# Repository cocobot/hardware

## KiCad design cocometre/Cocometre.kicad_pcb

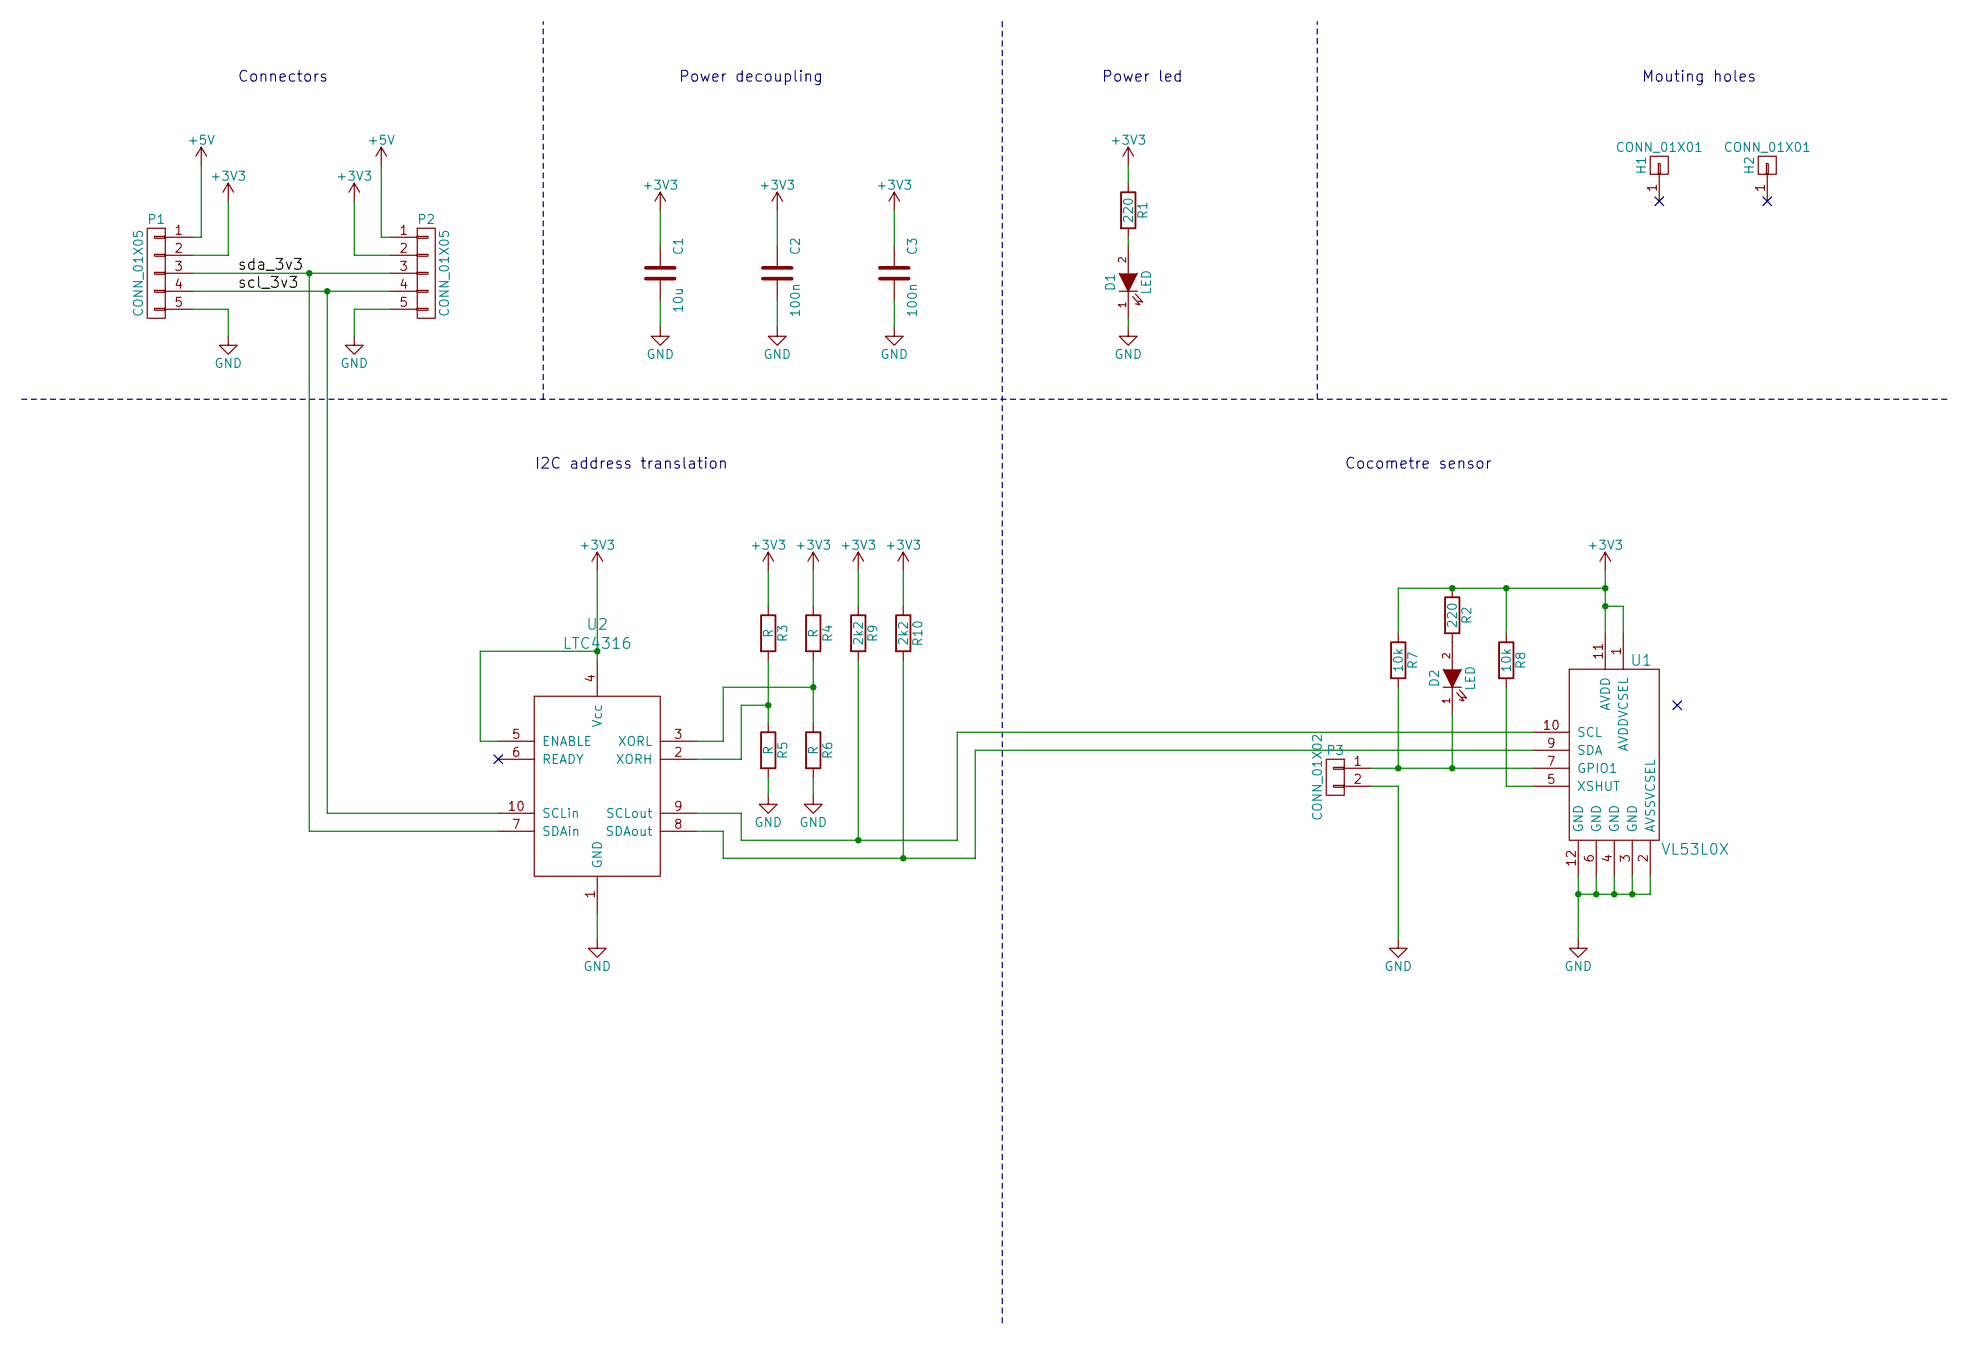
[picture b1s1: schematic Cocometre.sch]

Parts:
C1: 10u; C_0805_HandSoldering
C2, C3: 100n; C_0603_HandSoldering
D1, D2: LED; LED_0805
H1, H2: CONN_01X01; MountingHole_3.2mm_M3
P1, P2: CONN_01X05; Socket_MOLEX-KK-RM2-54mm_Lock_5pin_straight
P3: CONN_01X02; Socket_MOLEX-KK-RM2-54mm_Lock_2pin_straight
R1, R2: 220; R_0603_HandSoldering
R3, R4, R5, R6: R; R_0603_HandSoldering
R7, R8: 10k; R_0603_HandSoldering
R9, R10: 2k2; R_0603_HandSoldering
U1: VL53L0X
U2: LTC4316; MSOP-10

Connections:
+3V3: C1.1, C2.1, C3.1, P1.2, P2.2, R1.1, R2.1, R3.1, R4.1, R7.1, R8.1, R9.1, R10.1, U1.1 (AVDDVCSEL), U1.11 (AVDD), U2.4 (Vcc), U2.5 (ENABLE)
+5V: P1.1, P2.1
/scl_3v3: P1.4, P2.4, U2.10 (SCLin)
/sda_3v3: P1.3, P2.3, U2.7 (SDAin)
GND: C1.2, C2.2, C3.2, D1.1 (K), P1.5, P2.5, P3.2, R5.2, R6.2, U1.2 (AVSSVCSEL), U1.3 (GND), U1.4 (GND), U1.6 (GND), U1.12 (GND), U2.1 (GND)
unnamed: D1.2 (A), R1.2
unnamed: D2.1 (K), P3.1, R7.2, U1.7 (GPIO1)
unnamed: D2.2 (A), R2.2
unnamed: R3.2, R5.1, U2.2 (XORH)
unnamed: R4.2, R6.1, U2.3 (XORL)
unnamed: R8.2, U1.5 (XSHUT)
unnamed: R9.2, U1.10 (SCL), U2.9 (SCLout)
unnamed: R10.2, U1.9 (SDA), U2.8 (SDAout)

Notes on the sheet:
Connectors
Power decoupling
I2C address translation
Cocometre sensor
Mouting holes
Power led

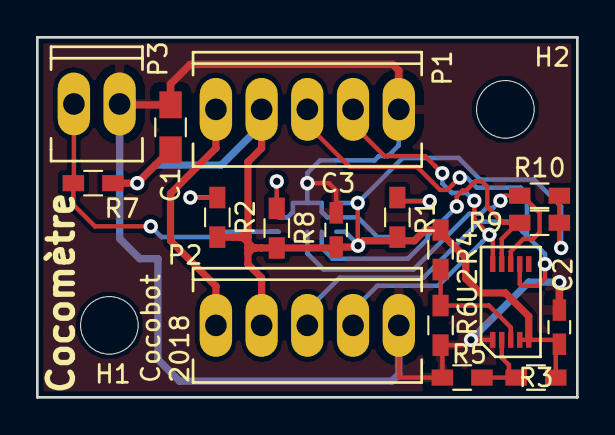
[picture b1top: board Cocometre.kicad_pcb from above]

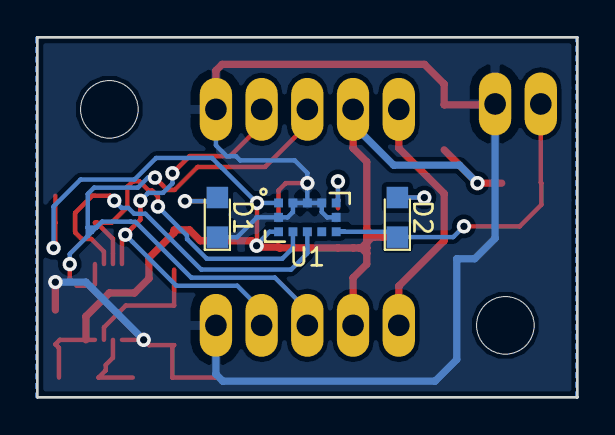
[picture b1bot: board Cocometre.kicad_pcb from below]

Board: 2 copper layers, 30.0 x 20.0 mm, 22 parts (3 on the bottom side), 13 nets.

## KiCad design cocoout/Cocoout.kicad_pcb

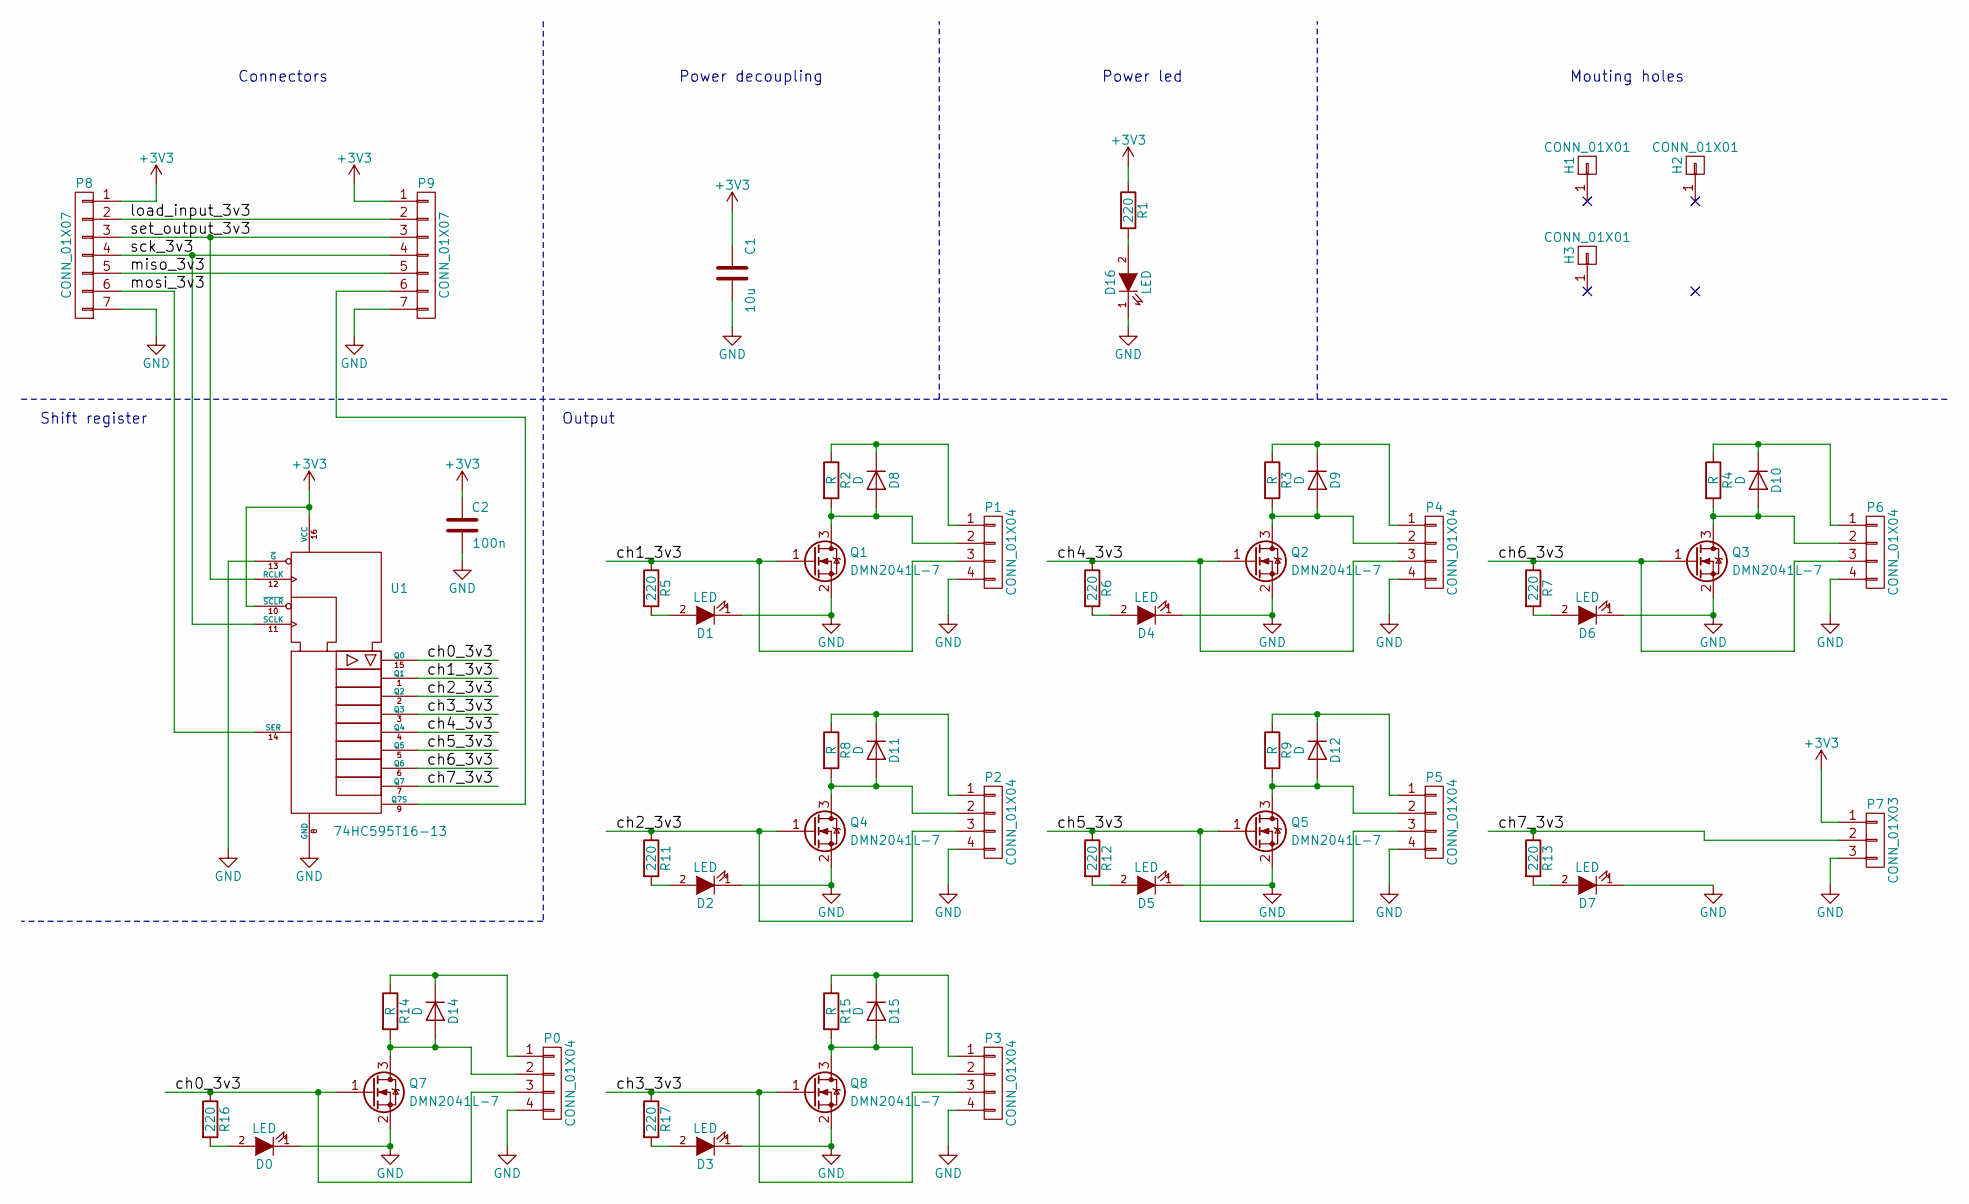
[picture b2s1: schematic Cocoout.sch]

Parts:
C1: 10u; C_0805_HandSoldering
C2: 100n; C_0603_HandSoldering
D0, D1, D2, D3, D4, D5, D6, D7, D16: LED; D_0805
D8, D9, D10, D11, D12, D14, D15: D; D_SMA_Handsoldering
H1, H2, H3: CONN_01X01; MountingHole_3.2mm_M3
P0, P1, P2, P3, P4, P5, P6: CONN_01X04; Socket_MOLEX-KK-RM2-54mm_Lock_4pin_straight
P7: CONN_01X03; Socket_MOLEX-KK-RM2-54mm_Lock_3pin_straight
P8, P9: CONN_01X07; Socket_MOLEX-KK-RM2-54mm_Lock_7pin_straight
Q1, Q2, Q3, Q4, Q5, Q7, Q8: DMN2041L-7; SOT-23
R1, R5, R6, R7, R11, R12, R13, R16, R17: 220; R_0603_HandSoldering
R2, R3, R4, R8, R9, R14, R15: R; R_0603_HandSoldering
U1: 74HC595T16-13; TSSOP-16_4.4x5mm_Pitch0.65mm

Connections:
+3V3: C1.1, C2.1, P7.1, P8.1, P9.1, R1.1, U1.10 (~SCLR), U1.16 (VCC)
/ch0_3v3: P0.3, Q7.1 (G), R16.1, U1.15 (Q0)
/ch1_3v3: P1.3, Q1.1 (G), R5.1, U1.1 (Q1)
/ch2_3v3: P2.3, Q4.1 (G), R11.1, U1.2 (Q2)
/ch3_3v3: P3.3, Q8.1 (G), R17.1, U1.3 (Q3)
/ch4_3v3: P4.3, Q2.1 (G), R6.1, U1.4 (Q4)
/ch5_3v3: P5.3, Q5.1 (G), R12.1, U1.5 (Q5)
/ch6_3v3: P6.3, Q3.1 (G), R7.1, U1.6 (Q6)
/ch7_3v3: P7.2, R13.1, U1.7 (Q7)
/load_input_3v3: P8.2, P9.2
/miso_3v3: P8.5, P9.5
/mosi_3v3: P8.6, U1.14 (SER)
/sck_3v3: P8.4, P9.4, U1.11 (SCLK)
/set_output_3v3: P8.3, P9.3, U1.12 (RCLK)
GND: C1.2, C2.2, D0.1 (K), D1.1 (K), D2.1 (K), D3.1 (K), D4.1 (K), D5.1 (K), D6.1 (K), D7.1 (K), D16.1 (K), P0.4, P1.4, P2.4, P3.4, P4.4, P5.4, P6.4, P7.3, P8.7, P9.7, Q1.2 (S), Q2.2 (S), Q3.2 (S), Q4.2 (S), Q5.2 (S), Q7.2 (S), Q8.2 (S), U1.8 (GND), U1.13 (~G)
unnamed: D0.2 (A), R16.2
unnamed: D1.2 (A), R5.2
unnamed: D2.2 (A), R11.2
unnamed: D3.2 (A), R17.2
unnamed: D4.2 (A), R6.2
unnamed: D5.2 (A), R12.2
unnamed: D6.2 (A), R7.2
unnamed: D7.2 (A), R13.2
unnamed: D8.1 (K), P1.1, R2.1
unnamed: D8.2 (A), P1.2, Q1.3 (D), R2.2
unnamed: D9.1 (K), P4.1, R3.1
unnamed: D9.2 (A), P4.2, Q2.3 (D), R3.2
unnamed: D10.1 (K), P6.1, R4.1
unnamed: D10.2 (A), P6.2, Q3.3 (D), R4.2
unnamed: D11.1 (K), P2.1, R8.1
unnamed: D11.2 (A), P2.2, Q4.3 (D), R8.2
unnamed: D12.1 (K), P5.1, R9.1
unnamed: D12.2 (A), P5.2, Q5.3 (D), R9.2
unnamed: D14.1 (K), P0.1, R14.1
unnamed: D14.2 (A), P0.2, Q7.3 (D), R14.2
unnamed: D15.1 (K), P3.1, R15.1
unnamed: D15.2 (A), P3.2, Q8.3 (D), R15.2
unnamed: D16.2 (A), R1.2
unnamed: P9.6, U1.9 (Q7S)

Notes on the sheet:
Connectors
Power decoupling
Mouting holes
Power led
Output
Shift register

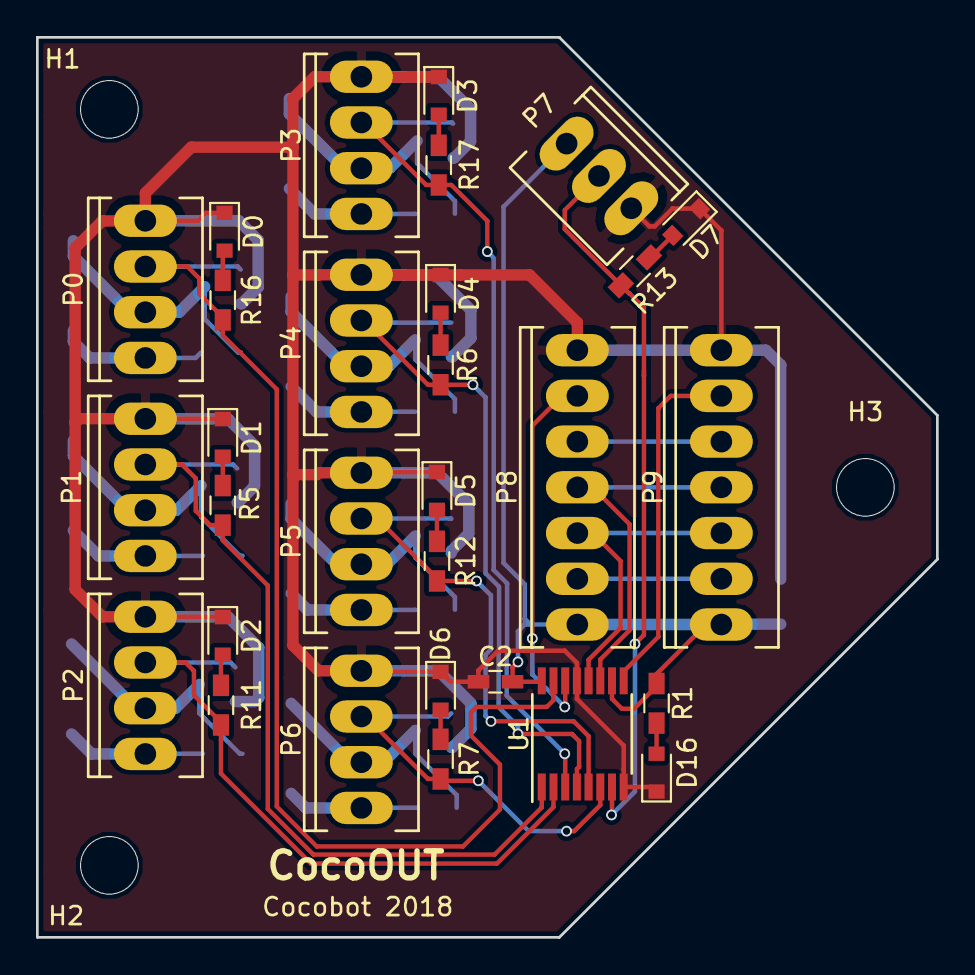
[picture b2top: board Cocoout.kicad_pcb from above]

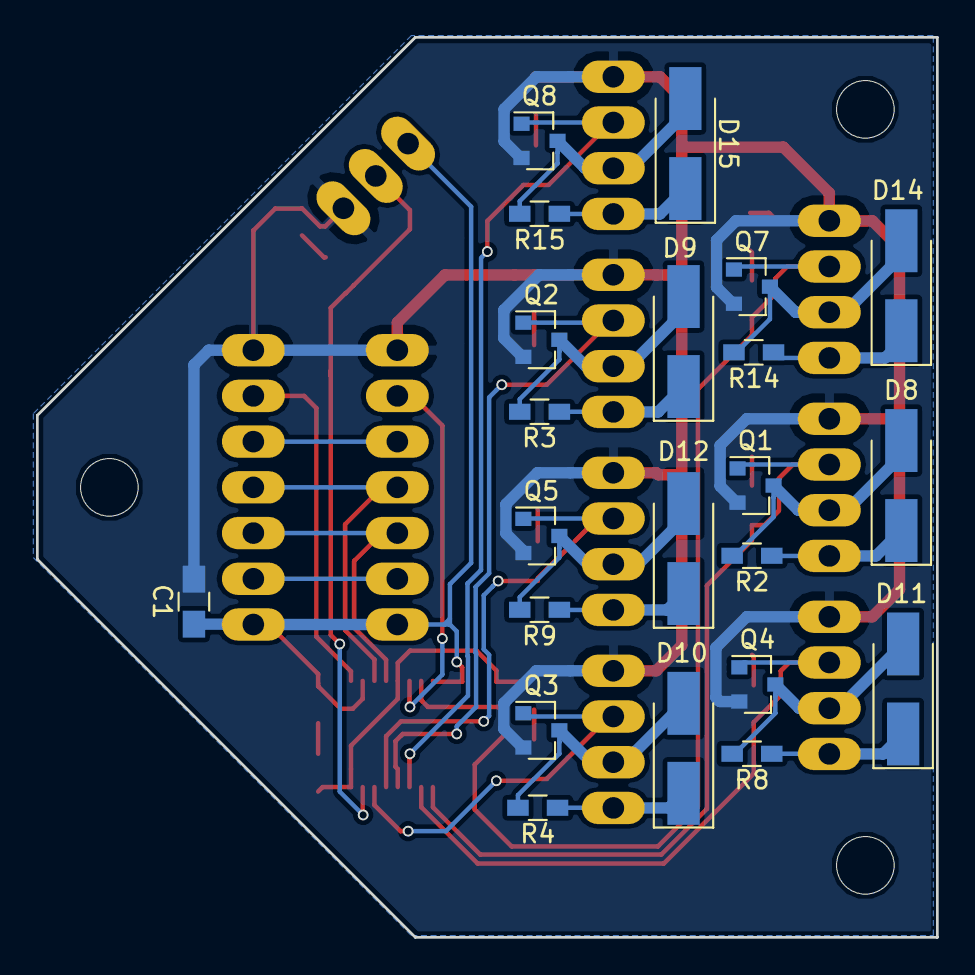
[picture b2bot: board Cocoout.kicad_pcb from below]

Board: 2 copper layers, 50.0 x 50.0 mm, 55 parts (22 on the bottom side), 39 nets.

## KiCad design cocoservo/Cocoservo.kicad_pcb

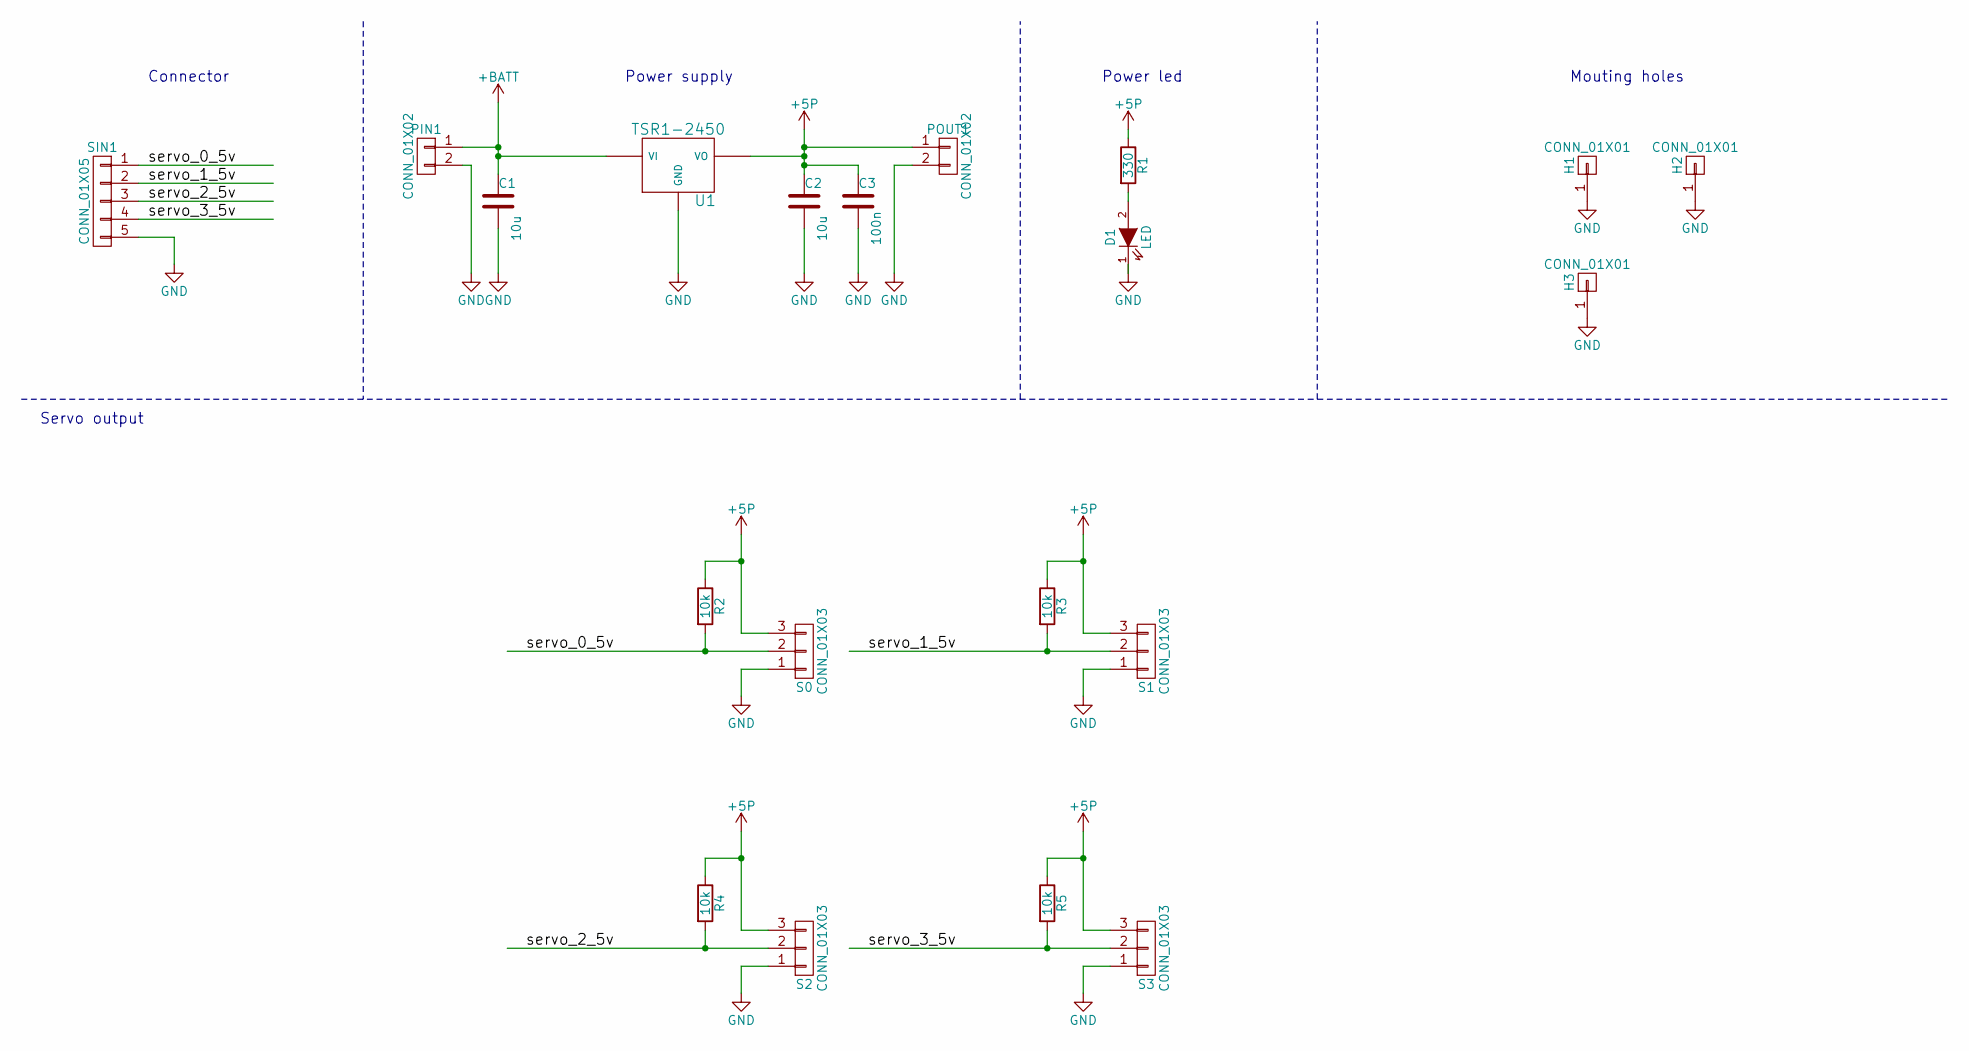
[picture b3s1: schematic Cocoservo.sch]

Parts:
C1, C2: 10u; C_0805_HandSoldering
C3: 100n; C_0603_HandSoldering
D1: LED; LED_0805
H1, H2, H3: CONN_01X01; MountingHole_3.2mm_M3
PIN1: CONN_01X02; Socket_MOLEX-KK-RM2-54mm_Lock_2pin_straight
POUT1: CONN_01X02; Socket_MOLEX-KK-RM2-54mm_Lock_2pin_straight
R1: 330; R_0603_HandSoldering
R2, R3, R4, R5: 10k; R_0603_HandSoldering
S0, S1, S2, S3: CONN_01X03; Socket_MOLEX-KK-RM2-54mm_Lock_3pin_straight
SIN1: CONN_01X05; Socket_MOLEX-KK-RM2-54mm_Lock_5pin_straight
U1: TSR1-2450; TSR-1

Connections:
+5P: C2.1, C3.1, POUT1.1, R1.1, R2.1, R3.1, R4.1, R5.1, S0.3, S1.3, S2.3, S3.3, U1.3 (VO)
+BATT: C1.1, PIN1.1, U1.1 (VI)
/servo_0_5v: R2.2, S0.2, SIN1.1
/servo_1_5v: R3.2, S1.2, SIN1.2
/servo_2_5v: R4.2, S2.2, SIN1.3
/servo_3_5v: R5.2, S3.2, SIN1.4
GND: C1.2, C2.2, C3.2, D1.1 (K), H1.1, H2.1, H3.1, PIN1.2, POUT1.2, S0.1, S1.1, S2.1, S3.1, SIN1.5, U1.2 (GND)
unnamed: D1.2 (A), R1.2

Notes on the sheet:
Connector
Mouting holes
Power led
Servo output
Power supply

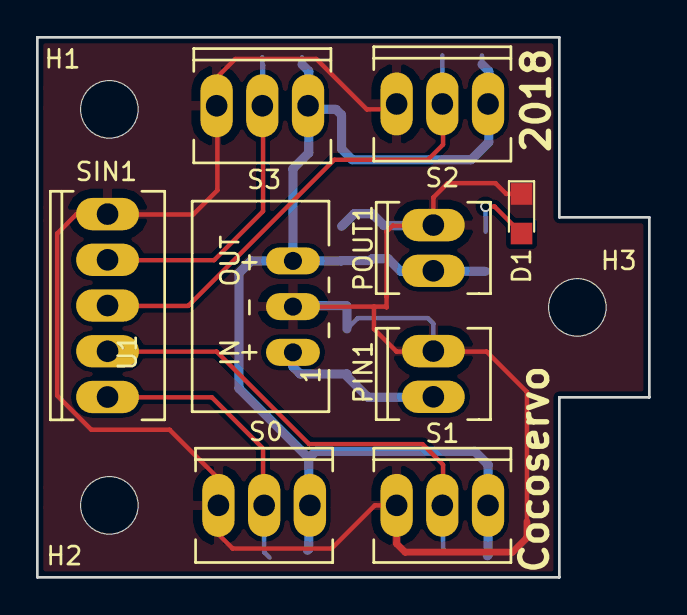
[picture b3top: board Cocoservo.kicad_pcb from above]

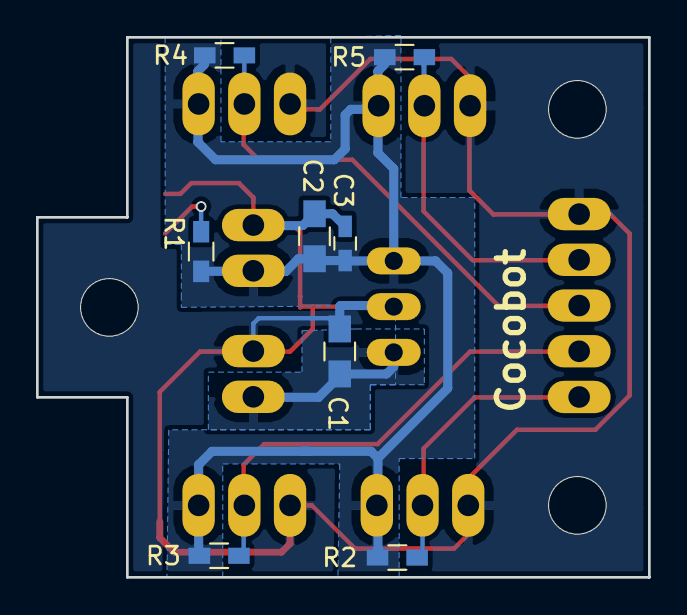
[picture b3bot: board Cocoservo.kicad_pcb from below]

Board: 2 copper layers, 34.0 x 30.0 mm, 20 parts (8 on the bottom side), 8 nets.

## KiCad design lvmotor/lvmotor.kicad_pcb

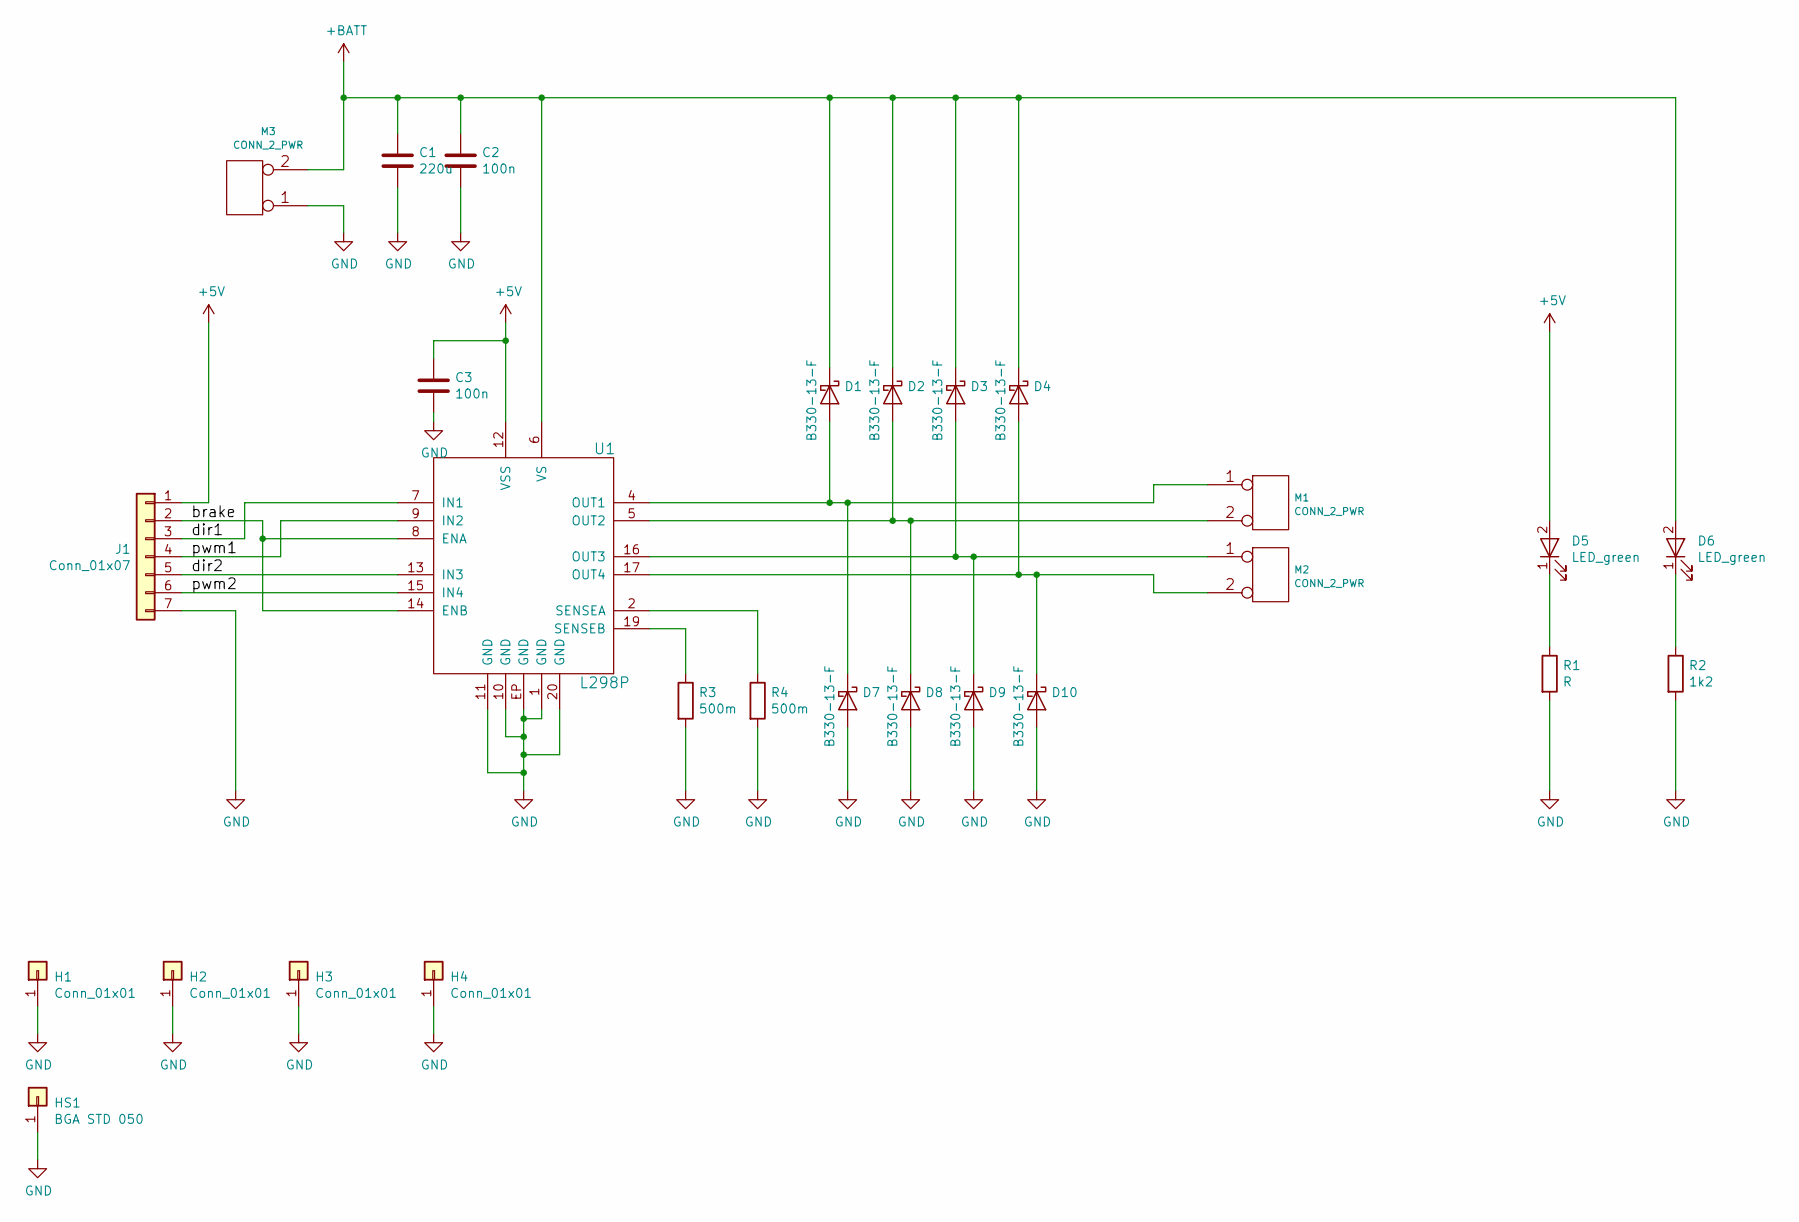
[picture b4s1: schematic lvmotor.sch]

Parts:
C1: 220u; CP_Elec_10x10
C2: 100n; C_0805
C3: 100n; C_0603
D1, D2, D3, D4, D7, D8, D9, D10: B330-13-F; D_SMC
D5, D6: LED_green; LED_0805
H1, H2, H3, H4: Conn_01x01; MountingHole_3.2mm_M3
HS1: BGA STD 050; BGA_STD_050
J1: Conn_01x07; Socket_MOLEX-KK-RM2-54mm_Lock_7pin_straight
M1, M2, M3: CONN_2_PWR; TerminalBlock_WAGO-236_2Stift_RM5mm_2pol
R1: R; R_0603
R2: 1k2; R_0603
R3, R4: 500m; R_2512
U1: L298P; PowerSO20

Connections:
+5V: C3.1, D5.2 (A), J1.1, U1.12 (VSS)
+BATT: C1.1, C2.1, D1.1 (K), D2.1 (K), D3.1 (K), D4.1 (K), D6.2 (A), M3.2 (PM), U1.6 (VS)
/brake: J1.2, U1.8 (ENA), U1.14 (ENB)
/dir1: J1.3, U1.7 (IN1)
/dir2: J1.5, U1.13 (IN3)
/pwm1: J1.4, U1.9 (IN2)
/pwm2: J1.6, U1.15 (IN4)
GND: C1.2, C2.2, C3.2, D7.2 (A), D8.2 (A), D9.2 (A), D10.2 (A), H1.1, H2.1, H3.1, H4.1, HS1.1, J1.7, M3.1, R1.2, R2.2, R3.2, R4.2, U1.1 (GND), U1.10 (GND), U1.11 (GND), U1.20 (GND), U1.EP (GND)
unnamed: D1.2 (A), D7.1 (K), M1.1, U1.4 (OUT1)
unnamed: D2.2 (A), D8.1 (K), M1.2 (PM), U1.5 (OUT2)
unnamed: D3.2 (A), D9.1 (K), M2.1, U1.16 (OUT3)
unnamed: D5.1 (K), R1.1
unnamed: D6.1 (K), R2.1
unnamed: D4.2 (A), D10.1 (K), M2.2 (PM), U1.17 (OUT4)
unnamed: R3.1, U1.19 (SENSEB)
unnamed: R4.1, U1.2 (SENSEA)

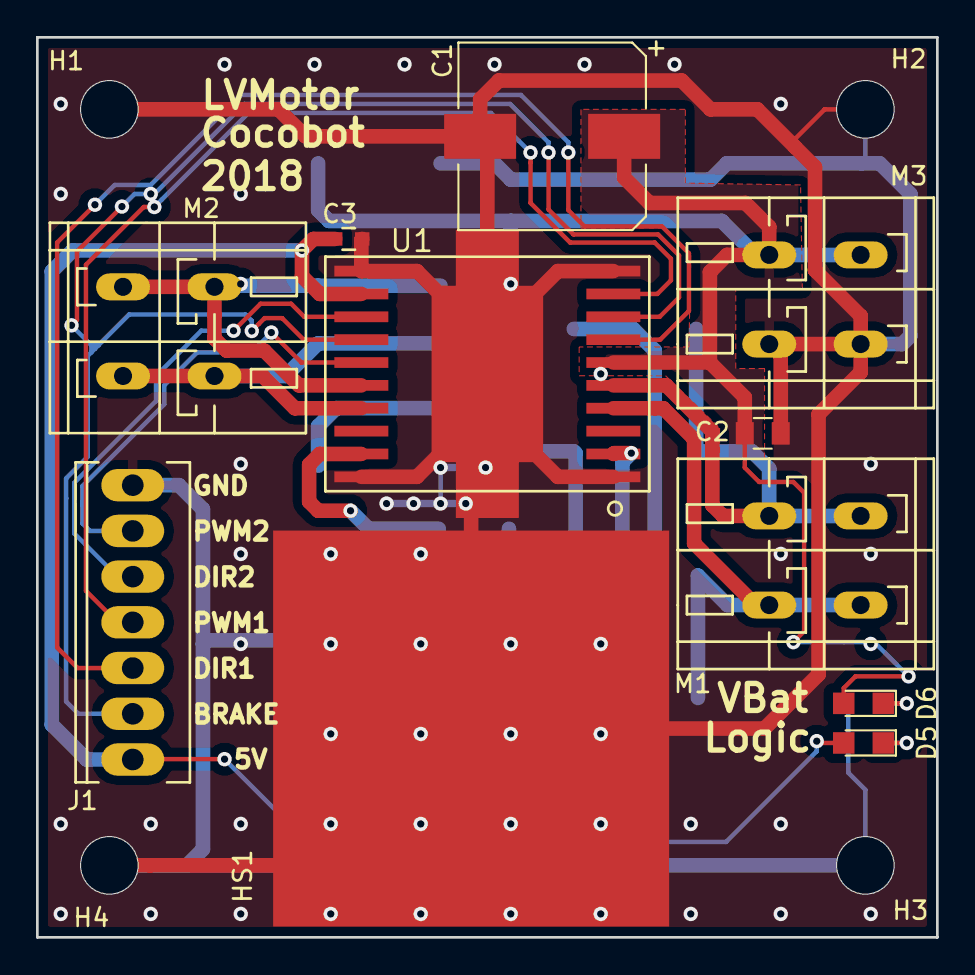
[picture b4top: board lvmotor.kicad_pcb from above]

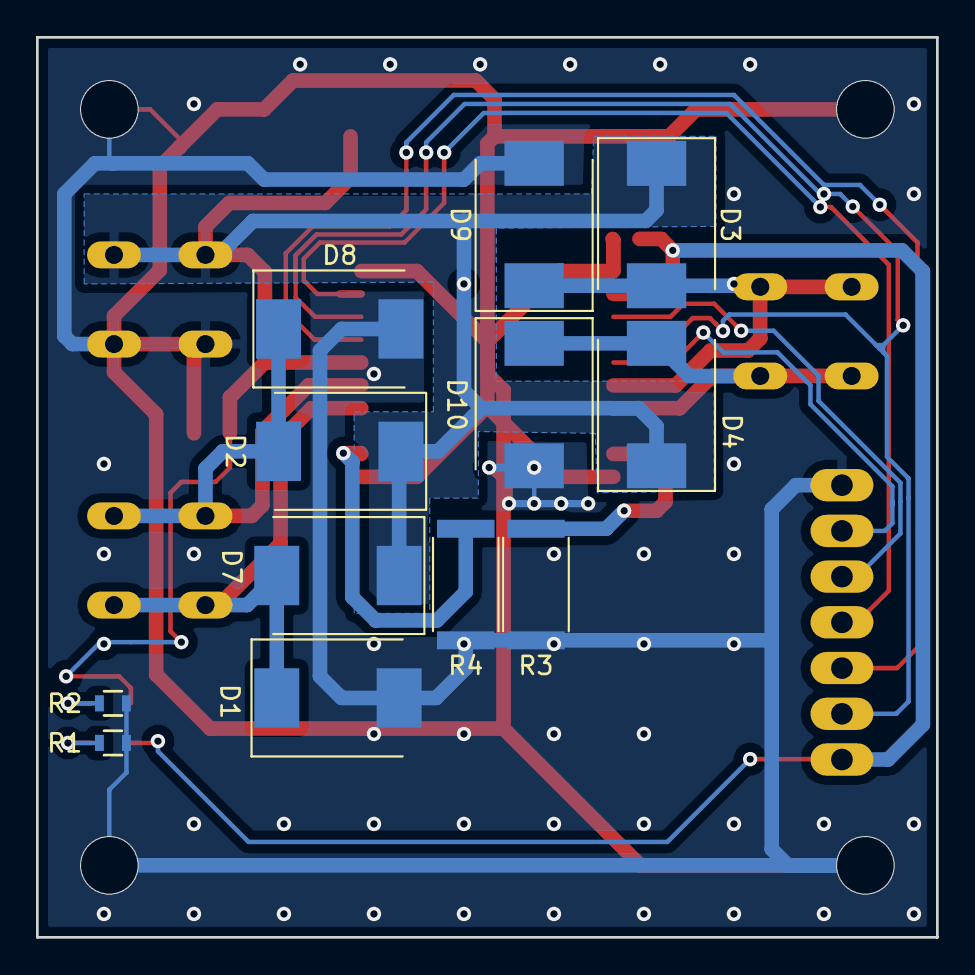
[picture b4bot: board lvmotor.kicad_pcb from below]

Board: 2 copper layers, 50.0 x 50.0 mm, 27 parts (12 on the bottom side), 16 nets.

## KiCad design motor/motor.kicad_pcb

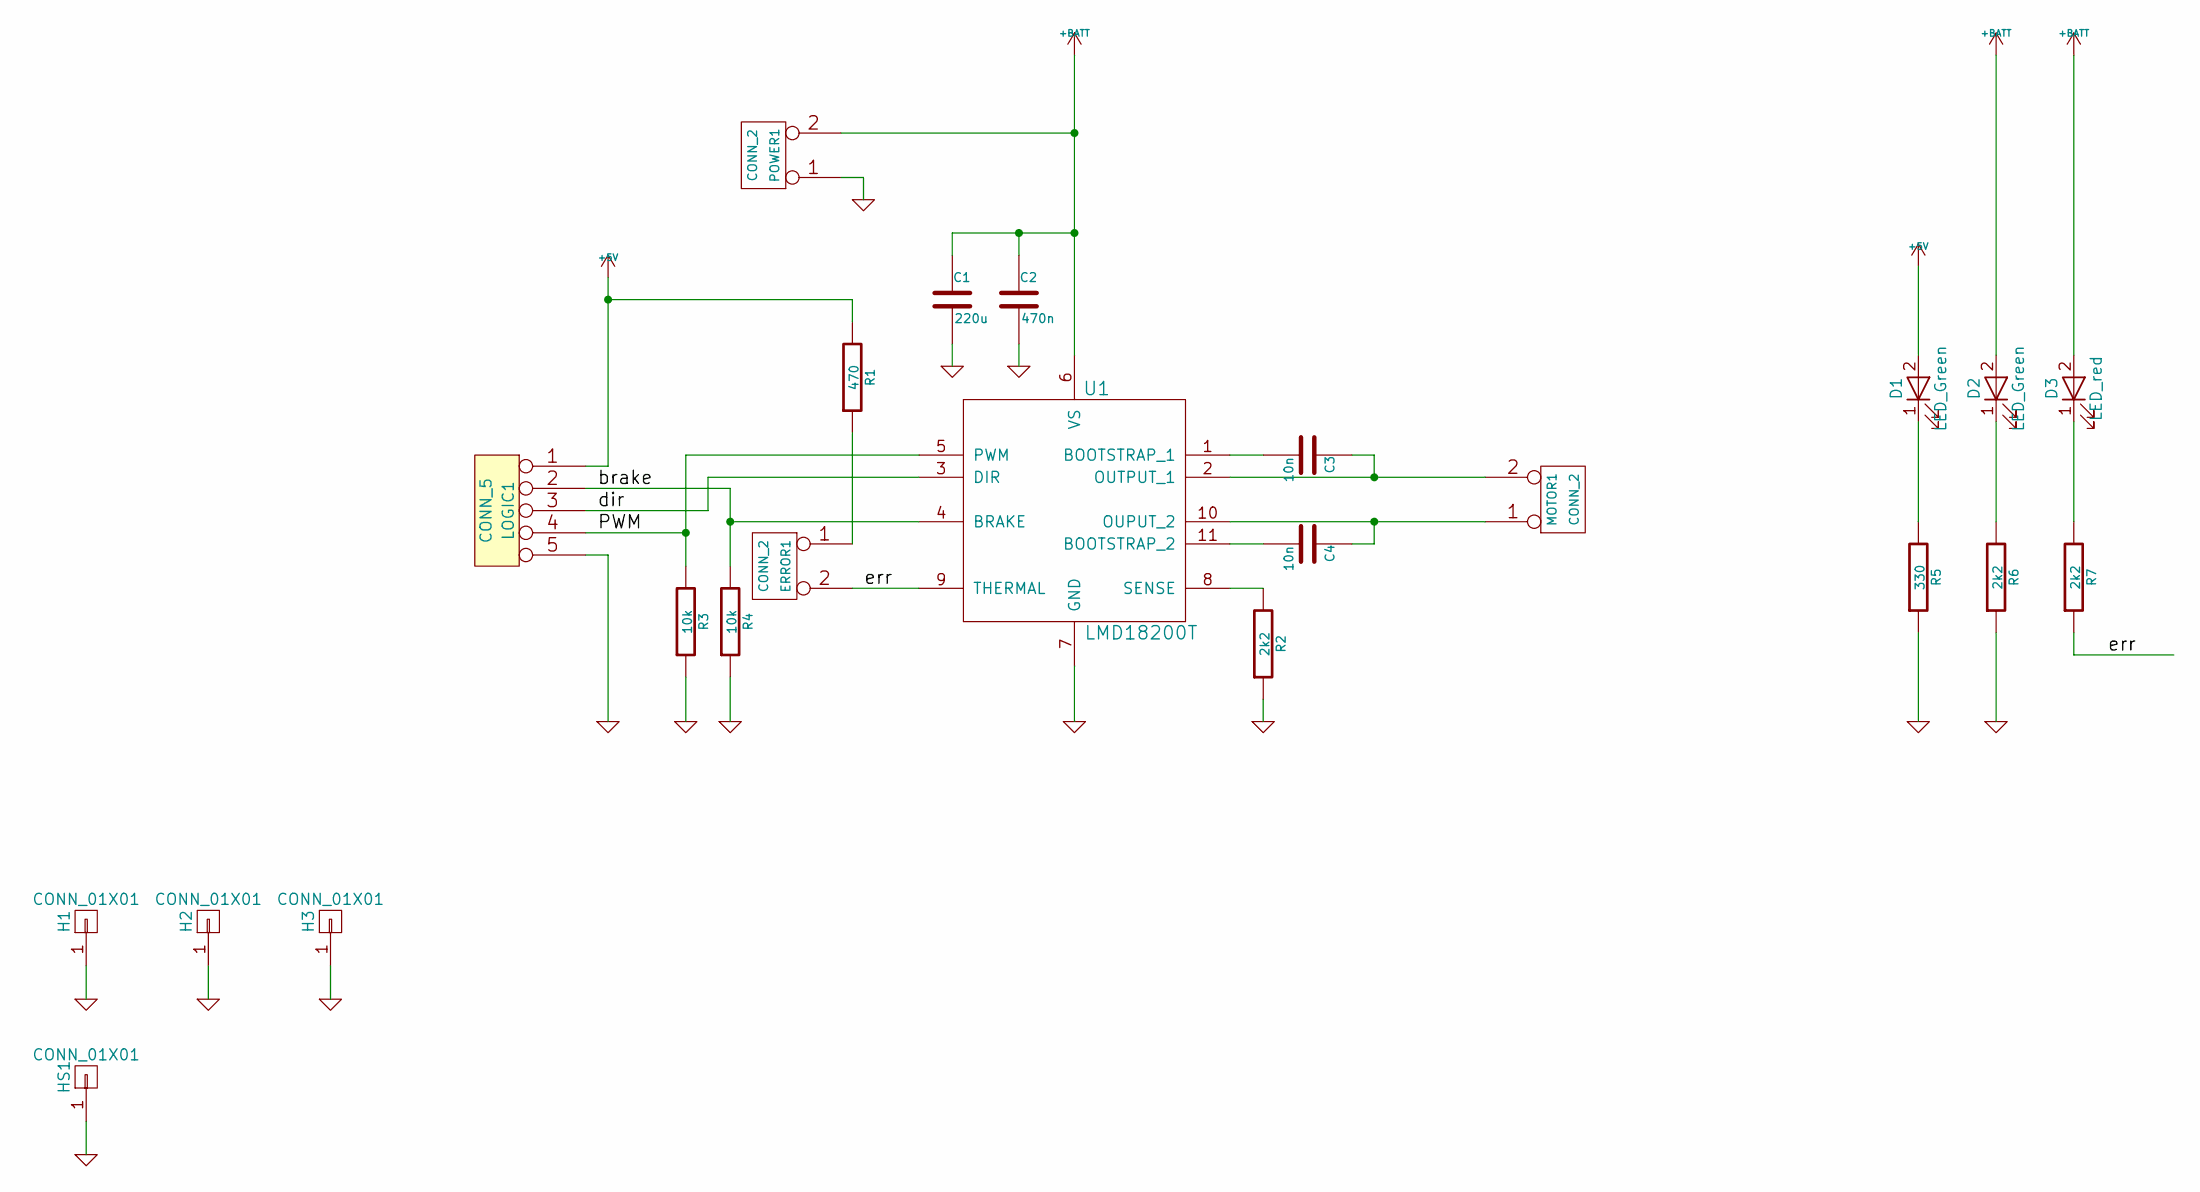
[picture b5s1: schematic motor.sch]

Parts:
C1: 220u; CP_Elec_10x10
C2: 470n; C_0805
C3, C4: 10n; C_0805
D1, D2: LED_Green; LED_0805
D3: LED_red; LED_0805
ERROR1: CONN_2; Socket_MOLEX-KK-RM2-54mm_Lock_2pin_straight
H1, H2, H3: CONN_01X01; MountingHole_3.2mm_M3
HS1: CONN_01X01; SK409-25_4STC
LOGIC1: CONN_5; Socket_MOLEX-KK-RM2-54mm_Lock_5pin_straight
MOTOR1: CONN_2; TerminalBlock_WAGO-236_2Stift_RM5mm_2pol
POWER1: CONN_2; TerminalBlock_WAGO-236_2Stift_RM5mm_2pol
R1: 470; R_0603
R2, R6, R7: 2k2; R_0603
R3, R4: 10k; R_0603
R5: 330; R_0603
U1: LMD18200T; NDJ0011B

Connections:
+5V: D1.2 (A), LOGIC1.1, R1.2
+BATT: C1.1, C2.1, D2.2 (A), D3.2 (A), POWER1.2 (PM), U1.6 (VS)
/PWM: LOGIC1.4, R3.2, U1.5 (PWM)
/brake: LOGIC1.2, R4.2, U1.4 (BRAKE)
/dir: LOGIC1.3, U1.3 (DIR)
/err: ERROR1.2 (PM), R7.1, U1.9 (THERMAL)
GND: C1.2, C2.2, H1.1, H2.1, H3.1, HS1.1, LOGIC1.5, POWER1.1, R2.1, R3.1, R4.1, R5.1, R6.1, U1.7 (GND)
unnamed: C3.1, MOTOR1.2 (PM), U1.2 (OUTPUT_1)
unnamed: C3.2, U1.1 (BOOTSTRAP_1)
unnamed: C4.1, MOTOR1.1, U1.10 (OUPUT_2)
unnamed: C4.2, U1.11 (BOOTSTRAP_2)
unnamed: D1.1 (K), R5.2
unnamed: D2.1 (K), R6.2
unnamed: D3.1 (K), R7.2
unnamed: ERROR1.1, R1.1
unnamed: R2.2, U1.8 (SENSE)
